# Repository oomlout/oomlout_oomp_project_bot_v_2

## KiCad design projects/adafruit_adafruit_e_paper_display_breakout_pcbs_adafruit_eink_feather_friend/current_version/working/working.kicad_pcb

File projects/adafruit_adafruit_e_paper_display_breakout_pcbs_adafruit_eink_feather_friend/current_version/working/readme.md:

# adafruit_e_paper_display_breakout_pcbs
 
## summary 
* id: adafruit_adafruit_e_paper_display_breakout_pcbs_adafruit_eink_feather_friend
* user: adafruit
* name: adafruit_e_paper_display_breakout_pcbs
* board: adafruit_eink_feather_friend
* repo: https://github.com/adafruit/Adafruit-E-Paper-Display-Breakout-PCBs

* src_file_repo_sch: 
* src_file_repo_sch_link: https://github.com/adafruit/Adafruit-E-Paper-Display-Breakout-PCBs/tree/master/
* full details link: https://github.com/oomlout/oomlout_oomp_project_bot_v_2/tree/main/projects/adafruit_adafruit_e_paper_display_breakout_pcbs_adafruit_eink_feather_friend/current_version/working  

## schematic  
  
[schematic (pdf)](working_schematic.pdf) 

## pcb  

[board (pdf)](working.pdf)  

## working_bom
| Id | Designator | Footprint | Quantity | Designation | Supplier and ref |  | None | 
| --- | --- | --- | --- | --- | --- | --- | --- | 
| 1 | U$5,U$3,U$4,U$6 | MOUNTINGHOLE_2.5_PLATED | 4 | MOUNTINGHOLE2.5 |  |  | [''] | 
| 2 | EINK1 | EINK_154IN | 1 | EINK_EPD0231EINK_154IN_200X200 |  |  | [''] | 
| 3 | X1 | MICROSD | 1 | MICROSD |  |  | [''] | 
| 4 | IC1 | TSSOP20 | 1 | 74LVC245PW |  |  | [''] | 
| 5 | R6,R1,R5,R2,R3 | 0805-NO | 5 | 100K |  |  | [''] | 
| 6 | C3,C4,C16,C22,C23 | 0805-NO | 5 | 1uF/25V |  |  | [''] | 
| 7 | FID3,FID2,FID1 | FIDUCIAL_1MM | 3 | FIDUCIAL_1MM |  |  | [''] | 
| 8 | C21,C20 | 0805-NO | 2 | 10ÂµF |  |  | [''] | 
| 9 | D3,D1,D2 | SOD-123 | 3 | MBR0530 |  |  | [''] | 
| 10 | U$28 | ADAFRUIT_TEXT_20MM | 1 |  |  |  | [''] | 
| 11 | L1 | INDUCTOR_4X4MM_NR401 | 1 | 10uH |  |  | [''] | 
| 12 | C6,C2 | 0805-NO | 2 | 1uF/10V |  |  | [''] | 
| 13 | R4 | 0805_10MGAP | 1 | 0.47ohm |  |  | [''] | 
| 14 | C24 | 0805-NO | 1 | 1uF/6V |  |  | [''] | 
| 15 | Q5 | SOT23-3 | 1 | IRLML0100 |  |  | [''] | 
| 16 | U2 | SOT23-5 | 1 | MIC5225-3.3 |  |  | [''] | 
| 17 | U$9 | PCBFEAT-REV-040 | 1 |  |  |  | [''] | 
| 18 | C15 | 0805-NO | 1 | 10uF/10V+ |  |  | [''] | 
| 19 | C1 | 0805_10MGAP | 1 | 1uF |  |  | [''] | 
| 20 | C5 | 0805-NO | 1 | 4.7uF/25V |  |  | [''] | 
| 21 | C8,C7 | 0805-NO | 2 | 1uF |  |  | [''] | 
| 22 | U4 | SOIC8_150MIL | 1 | 23K640-I/SN |  |  | [''] | 
| 23 | JP2 | 1X13_ROUND_70 | 1 |  |  |  | [''] | 

## bom_schematic
| Ref | Qnty | Value | Cmp name | Footprint | Description | Vendor | DNP | 
| --- | --- | --- | --- | --- | --- | --- | --- | 
| C1 | 1 | 1uF | CAP_CERAMIC0805_10MGAP | working:0805_10MGAP |  |  |  | 
| C2, C6 | 2 | 1uF/10V | CAP_CERAMIC0805-NOOUTLINE | working:0805-NO |  |  |  | 
| C3, C4, C16, C22, C23 | 5 | 1uF/25V | CAP_CERAMIC0805-NOOUTLINE | working:0805-NO |  |  |  | 
| C5 | 1 | 4.7uF/25V | CAP_CERAMIC0805-NOOUTLINE | working:0805-NO |  |  |  | 
| C7, C8 | 2 | 1uF | CAP_CERAMIC0805-NOOUTLINE | working:0805-NO |  |  |  | 
| C15 | 1 | 10uF/10V+ | CAP_CERAMIC0805-NOOUTLINE | working:0805-NO |  |  |  | 
| C20, C21 | 2 | 10ÂµF | CAP_CERAMIC0805-NOOUTLINE | working:0805-NO |  |  |  | 
| C24 | 1 | 1uF/6V | CAP_CERAMIC0805-NOOUTLINE | working:0805-NO |  |  |  | 
| D1, D2, D3 | 3 | MBR0530 | DIODE-SCHOTTKYSOD-123 | working:SOD-123 |  |  |  | 
| EINK1 | 1 | EINK_EPD0231EINK_154IN_200X200 | EINK_EPD0231EINK_154IN_200X200 | working:EINK_154IN |  |  |  | 
| FID1, FID2, FID3 | 3 | FIDUCIAL_1MM | FIDUCIAL_1MM | working:FIDUCIAL_1MM |  |  |  | 
| IC1 | 1 | 74245TSSOP20 | 74245TSSOP20 | working:TSSOP20 |  |  |  | 
| JP2 | 1 | HEADER-1X13 | HEADER-1X13 | working:1X13_ROUND_70 |  |  |  | 
| L1 | 1 | 10uH | INDUCTORNR401 | working:INDUCTOR_4X4MM_NR401 |  |  |  | 
| Q5 | 1 | IRLML2060TRPBF | IRLML2060TRPBF | working:SOT23-3 |  |  |  | 
| R1, R2, R3, R5, R6 | 5 | 100K | RESISTOR0805_NOOUTLINE | working:0805-NO |  |  |  | 
| R4 | 1 | 0.47ohm | RESISTOR0805_10MGAP | working:0805_10MGAP |  |  |  | 
| U2 | 1 | MIC5225-3.3 | VREG_SOT23-5 | working:SOT23-5 |  |  |  | 
| U4 | 1 | 23K640-I/SN | SRAM_SPI_SOIC8 | working:SOIC8_150MIL |  |  |  | 
| U$3, U$4, U$5, U$6 | 4 | MOUNTINGHOLE2.5 | MOUNTINGHOLE2.5 | working:MOUNTINGHOLE_2.5_PLATED |  |  |  | 
| X1 | 1 | MICROSD | MICROSD | working:MICROSD |  |  |  | 

## mounting_holes
| x | y | package | value | ref | size | 
| --- | --- | --- | --- | --- | --- | 
| 0.0 | 0.0 | MOUNTINGHOLE_2.5_PLATED | MOUNTINGHOLE2.5 | U$3 | m3 | 
| 38.1 | 0.0 | MOUNTINGHOLE_2.5_PLATED | MOUNTINGHOLE2.5 | U$4 | m3 | 
| 0.0 | 38.1 | MOUNTINGHOLE_2.5_PLATED | MOUNTINGHOLE2.5 | U$5 | m3 | 
| 38.1 | 38.1 | MOUNTINGHOLE_2.5_PLATED | MOUNTINGHOLE2.5 | U$6 | m3 |

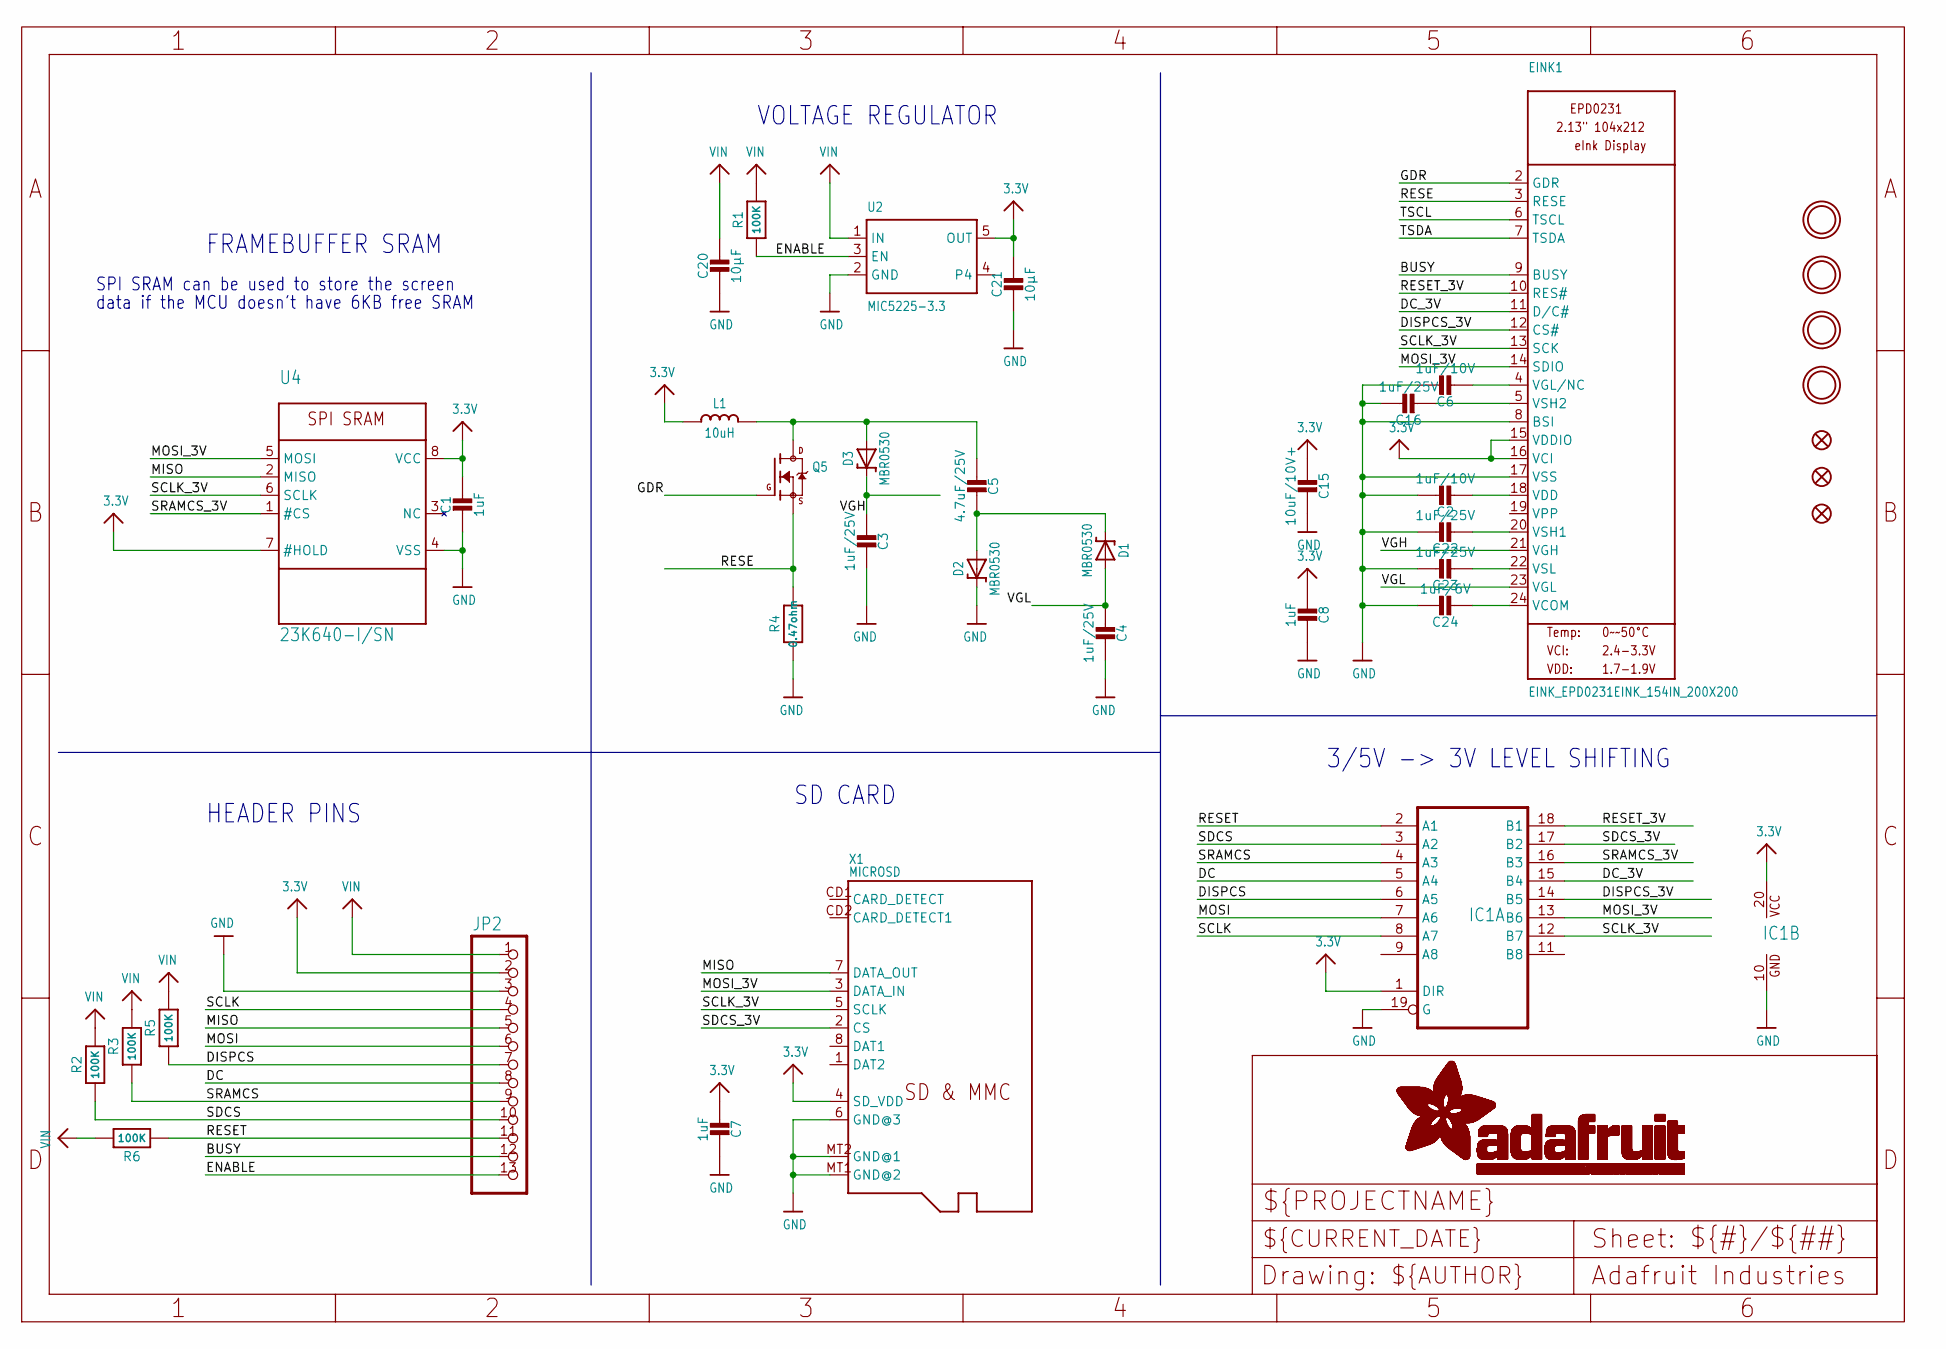
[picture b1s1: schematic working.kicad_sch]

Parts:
C1: 1uF; 0805_10MGAP
C2, C6: 1uF/10V; 0805-NO
C3, C4, C16, C22, C23: 1uF/25V; 0805-NO
C5: 4.7uF/25V; 0805-NO
C7, C8: 1uF; 0805-NO
C15: 10uF/10V+; 0805-NO
C20, C21: 10µF; 0805-NO
C24: 1uF/6V; 0805-NO
D1, D2, D3: MBR0530; SOD-123
EINK1: EINK_EPD0231EINK_154IN_200X200; EINK_154IN
FID1, FID2, FID3: FIDUCIAL_1MM
IC1: 74245TSSOP20; TSSOP20
JP2: HEADER-1X13; 1X13_ROUND_70
L1: 10uH; INDUCTOR_4X4MM_NR401
Q5: IRLML2060TRPBF; SOT23-3
R1, R2, R3, R5, R6: 100K; 0805-NO
R4: 0.47ohm; 0805_10MGAP
U2: MIC5225-3.3; SOT23-5
U4: 23K640-I/SN; SOIC8_150MIL
U$3, U$4, U$5, U$6: MOUNTINGHOLE2.5; MOUNTINGHOLE_2.5_PLATED
X1: MICROSD

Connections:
3.3V: C1.1, C7.1, C8.1, C15.2, C21.1, EINK1.15 (VDDIO), EINK1.16 (VCI), IC1.1 (DIR), IC1.20 (VCC), JP2.2, L1.P$2 (2), U2.5 (OUT), U4.7 (#HOLD), U4.8 (VCC), X1.4 (SD_VDD)
BUSY: EINK1.9 (BUSY), JP2.12
DC: IC1.5 (A4), JP2.8
DC_3V: EINK1.11 (D/C#), IC1.15 (B4)
DISPCS: IC1.6 (A5), JP2.7, R5.1
DISPCS_3V: EINK1.12 (CS#), IC1.14 (B5)
ENABLE: JP2.13, R1.1, U2.3 (EN)
GDR: EINK1.2 (GDR), Q5.1 (G)
GND: C1.2, C2.1, C3.2, C4.2, C6.1, C7.2, C8.2, C15.1, C16.1, C20.2, C21.2, C22.1, C23.1, C24.1, D2.C, EINK1.8 (BSI), EINK1.17 (VSS), IC1.10 (GND), IC1.19 (G), JP2.3, R4.2, U2.2 (GND), U4.4 (VSS), X1.6 (GND@3), X1.MT1 (GND@2), X1.MT2 (GND@1)
MISO: JP2.5, U4.2 (MISO), X1.7 (DATA_OUT)
MOSI: IC1.7 (A6), JP2.6
MOSI_3V: EINK1.14 (SDIO), IC1.13 (B6), U4.5 (MOSI), X1.3 (DATA_IN)
unnamed: C5.2, D1.C, D2.A
unnamed: C5.1, D3.A, L1.P$1 (1), Q5.3 (D)
unnamed: C16.2, EINK1.5 (VSH2)
unnamed: C2.2, EINK1.18 (VDD)
unnamed: C22.2, EINK1.20 (VSH1)
unnamed: C6.2, EINK1.4 (VGL/NC)
unnamed: C23.2, EINK1.22 (VSL)
unnamed: C24.2, EINK1.24 (VCOM)
RESE: EINK1.3 (RESE), Q5.2 (S), R4.1
RESET: IC1.2 (A1), JP2.11, R6.1
RESET_3V: EINK1.10 (RES#), IC1.18 (B1)
SCLK: IC1.8 (A7), JP2.4
SCLK_3V: EINK1.13 (SCK), IC1.12 (B7), U4.6 (SCLK), X1.5 (SCLK)
SDCS: IC1.3 (A2), JP2.10, R2.1
SDCS_3V: IC1.17 (B2), X1.2 (CS)
SRAMCS: IC1.4 (A3), JP2.9, R3.1
SRAMCS_3V: IC1.16 (B3), U4.1 (#CS)
TSCL: EINK1.6 (TSCL)
TSDA: EINK1.7 (TSDA)
VGH: C3.1, D3.C, EINK1.21 (VGH)
VGL: C4.1, D1.A, EINK1.23 (VGL)
VIN: C20.1, JP2.1, R1.2, R2.2, R3.2, R5.2, R6.2, U2.1 (IN)

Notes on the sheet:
HEADER PINS
VOLTAGE REGULATOR
SPI SRAM can be used to store the screen
FRAMEBUFFER SRAM
3/5V -> 3V LEVEL SHIFTING
SD CARD
data if the MCU doesn't have 6KB free SRAM

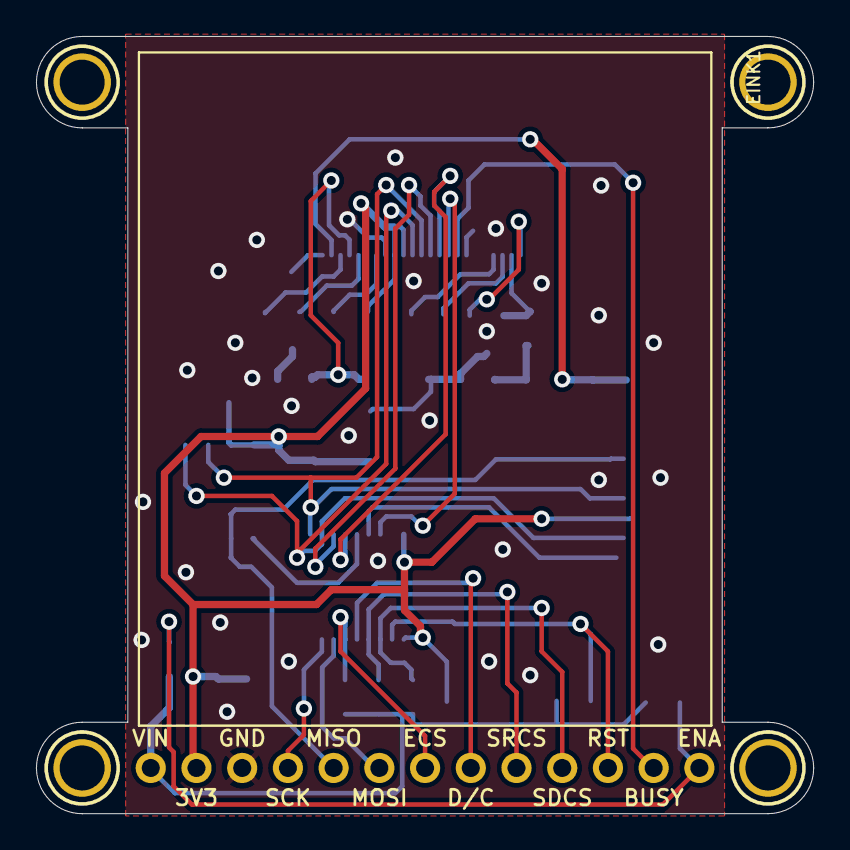
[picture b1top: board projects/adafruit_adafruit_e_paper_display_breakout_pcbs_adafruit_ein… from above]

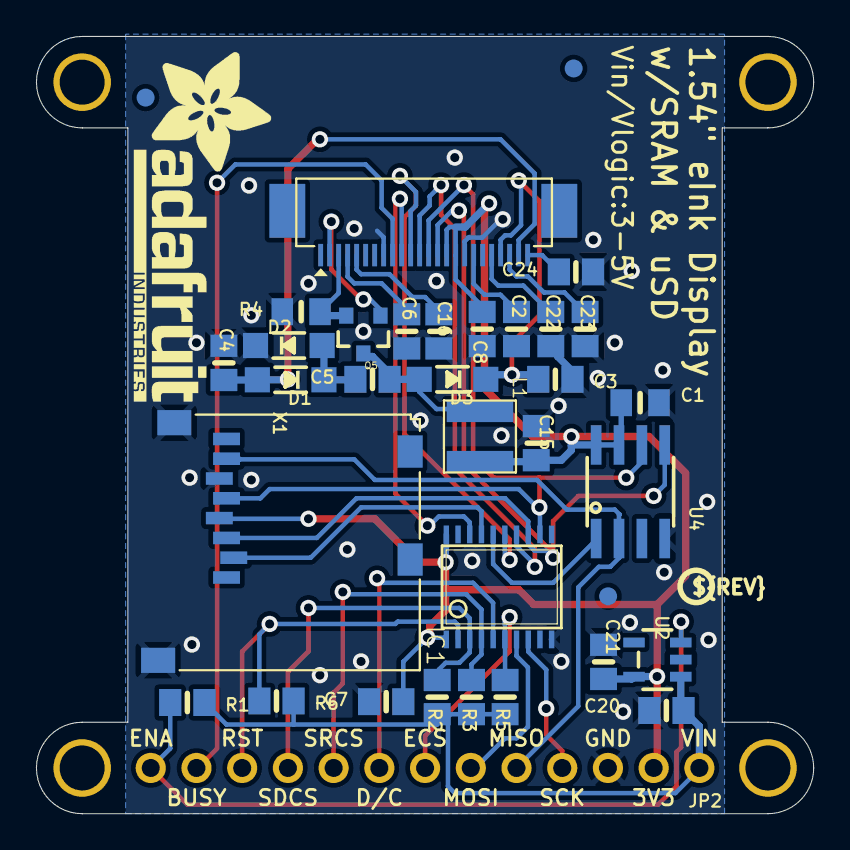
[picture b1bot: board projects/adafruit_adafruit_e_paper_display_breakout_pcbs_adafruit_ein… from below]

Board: 2 copper layers, 43.2 x 43.2 mm, 41 parts (36 on the bottom side), 32 nets.

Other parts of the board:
U$9: PCBFEAT-REV-040
U$28: ADAFRUIT_TEXT_20MM

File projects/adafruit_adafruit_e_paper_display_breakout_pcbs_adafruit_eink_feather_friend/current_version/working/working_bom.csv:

"Id";"Designator";"Footprint";"Quantity";"Designation";"Supplier and ref";
1;"U$5,U$3,U$4,U$6";"MOUNTINGHOLE_2.5_PLATED";4;"MOUNTINGHOLE2.5";;;
2;"EINK1";"EINK_154IN";1;"EINK_EPD0231EINK_154IN_200X200";;;
3;"X1";"MICROSD";1;"MICROSD";;;
4;"IC1";"TSSOP20";1;"74LVC245PW";;;
5;"R6,R1,R5,R2,R3";"0805-NO";5;"100K";;;
6;"C3,C4,C16,C22,C23";"0805-NO";5;"1uF/25V";;;
7;"FID3,FID2,FID1";"FIDUCIAL_1MM";3;"FIDUCIAL_1MM";;;
8;"C21,C20";"0805-NO";2;"10µF";;;
9;"D3,D1,D2";"SOD-123";3;"MBR0530";;;
10;"U$28";"ADAFRUIT_TEXT_20MM";1;"";;;
11;"L1";"INDUCTOR_4X4MM_NR401";1;"10uH";;;
12;"C6,C2";"0805-NO";2;"1uF/10V";;;
13;"R4";"0805_10MGAP";1;"0.47ohm";;;
14;"C24";"0805-NO";1;"1uF/6V";;;
15;"Q5";"SOT23-3";1;"IRLML0100";;;
16;"U2";"SOT23-5";1;"MIC5225-3.3";;;
17;"U$9";"PCBFEAT-REV-040";1;"";;;
18;"C15";"0805-NO";1;"10uF/10V+";;;
19;"C1";"0805_10MGAP";1;"1uF";;;
20;"C5";"0805-NO";1;"4.7uF/25V";;;
21;"C8,C7";"0805-NO";2;"1uF";;;
22;"U4";"SOIC8_150MIL";1;"23K640-I/SN";;;
23;"JP2";"1X13_ROUND_70";1;"";;;

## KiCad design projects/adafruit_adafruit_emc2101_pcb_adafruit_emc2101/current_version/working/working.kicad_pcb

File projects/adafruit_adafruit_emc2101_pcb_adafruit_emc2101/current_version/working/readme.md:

# adafruit_emc2101_pcb
 
## summary 
* id: adafruit_adafruit_emc2101_pcb_adafruit_emc2101
* user: adafruit
* name: adafruit_emc2101_pcb
* board: adafruit_emc2101
* repo: https://github.com/adafruit/Adafruit-EMC2101-PCB

* src_file_repo_sch: 
* src_file_repo_sch_link: https://github.com/adafruit/Adafruit-EMC2101-PCB/tree/main/
* full details link: https://github.com/oomlout/oomlout_oomp_project_bot_v_2/tree/main/projects/adafruit_adafruit_emc2101_pcb_adafruit_emc2101/current_version/working  

## schematic  
  
[schematic (pdf)](working_schematic.pdf) 

## pcb  

[board (pdf)](working.pdf)  

## working_bom
| Id | Designator | Footprint | Quantity | Designation | Supplier and ref |  | None | 
| --- | --- | --- | --- | --- | --- | --- | --- | 
| 1 | JP1 | 1X06_ROUND_70 | 1 |  |  |  | [''] | 
| 2 | JP2 | 1X04_ROUND | 1 |  |  |  | [''] | 
| 3 | CONN3,CONN4 | JST_SH4 | 2 | STEMMA_I2C_QT |  |  | [''] | 
| 4 | R1 | _0603MP | 1 | 10K |  |  | [''] | 
| 5 | FID4,FID3 | FIDUCIAL_1MM | 2 | FIDUCIAL_1MM |  |  | [''] | 
| 6 | C3,C2 | 0805-NO | 2 | 10uF |  |  | [''] | 
| 7 | U$1,U$21,U$19,U$17 | MOUNTINGHOLE_2.5_PLATED | 4 | MOUNTINGHOLE2.5 |  |  | [''] | 
| 8 | C1 | 0603-NO | 1 | 0.1uF |  |  | [''] | 
| 9 | D1 | CHIPLED_0603_NOOUTLINE | 1 | GREEN |  |  | [''] | 
| 10 | U2 | SOT23-5 | 1 | AP2112K-3.3 |  |  | [''] | 
| 11 | R3 | RESPACK_4X0603 | 1 | 10K |  |  | [''] | 
| 12 | X1 | MSOP8_0.65MM | 1 | EMC2101-AZCL |  |  | [''] | 
| 13 | U$22 | ADAFRUIT_3.5MM | 1 |  |  |  | [''] | 
| 14 | SJ1 | SOLDERJUMPER_CLOSEDWIRE | 1 | FAN |  |  | [''] | 
| 15 | U$31,U$30 | STEMMAQT | 2 |  |  |  | [''] | 
| 16 | U$25 | PCBFEAT-REV-040 | 1 |  |  |  | [''] | 
| 17 | SJ2 | SOLDERJUMPER_ARROW_NOPASTE | 1 | TACH |  |  | [''] | 

## bom_schematic
| Ref | Qnty | Value | Cmp name | Footprint | Description | Vendor | DNP | 
| --- | --- | --- | --- | --- | --- | --- | --- | 
| C1 | 1 | 0.1uF | CAP_CERAMIC0603_NO | working:0603-NO |  |  |  | 
| C2, C3 | 2 | 10uF | CAP_CERAMIC0805-NOOUTLINE | working:0805-NO |  |  |  | 
| CONN3, CONN4 | 2 | STEMMA_I2C_QT | STEMMA_I2C_QT | working:JST_SH4 |  |  |  | 
| D1 | 1 | GREEN | LED0603_NOOUTLINE | working:CHIPLED_0603_NOOUTLINE |  |  |  | 
| FID3, FID4 | 2 | FIDUCIAL_1MM | FIDUCIAL_1MM | working:FIDUCIAL_1MM |  |  |  | 
| JP1 | 1 | HEADER-1X670MIL | HEADER-1X670MIL | working:1X06_ROUND_70 |  |  |  | 
| JP2 | 1 | HEADER-1X4ROUND | HEADER-1X4ROUND | working:1X04_ROUND |  |  |  | 
| R1 | 1 | 10K | RESISTOR_0603MP | working:_0603MP |  |  |  | 
| R3 | 1 | 10K | RESISTOR_4PACK | working:RESPACK_4X0603 |  |  |  | 
| SJ1 | 1 | FAN | SOLDERJUMPERCLOSED | working:SOLDERJUMPER_CLOSEDWIRE |  |  |  | 
| SJ2 | 1 | TACH | SOLDERJUMPER | working:SOLDERJUMPER_ARROW_NOPASTE |  |  |  | 
| U2 | 1 | AP2112K-3.3 | VREG_SOT23-5 | working:SOT23-5 |  |  |  | 
| U$1, U$17, U$19, U$21 | 4 | MOUNTINGHOLE2.5 | MOUNTINGHOLE2.5 | working:MOUNTINGHOLE_2.5_PLATED |  |  |  | 
| X1 | 1 | EMC2101-AZCL | EMC2101-AZCL | working:MSOP8_0.65MM |  |  |  | 

## mounting_holes
| x | y | package | value | ref | size | 
| --- | --- | --- | --- | --- | --- | 
| 0.0 | 12.7 | MOUNTINGHOLE_2.5_PLATED | MOUNTINGHOLE2.5 | U$1 | m3 | 
| 20.32 | 12.7 | MOUNTINGHOLE_2.5_PLATED | MOUNTINGHOLE2.5 | U$17 | m3 | 
| 0.0 | 0.0 | MOUNTINGHOLE_2.5_PLATED | MOUNTINGHOLE2.5 | U$19 | m3 | 
| 20.32 | 0.0 | MOUNTINGHOLE_2.5_PLATED | MOUNTINGHOLE2.5 | U$21 | m3 |

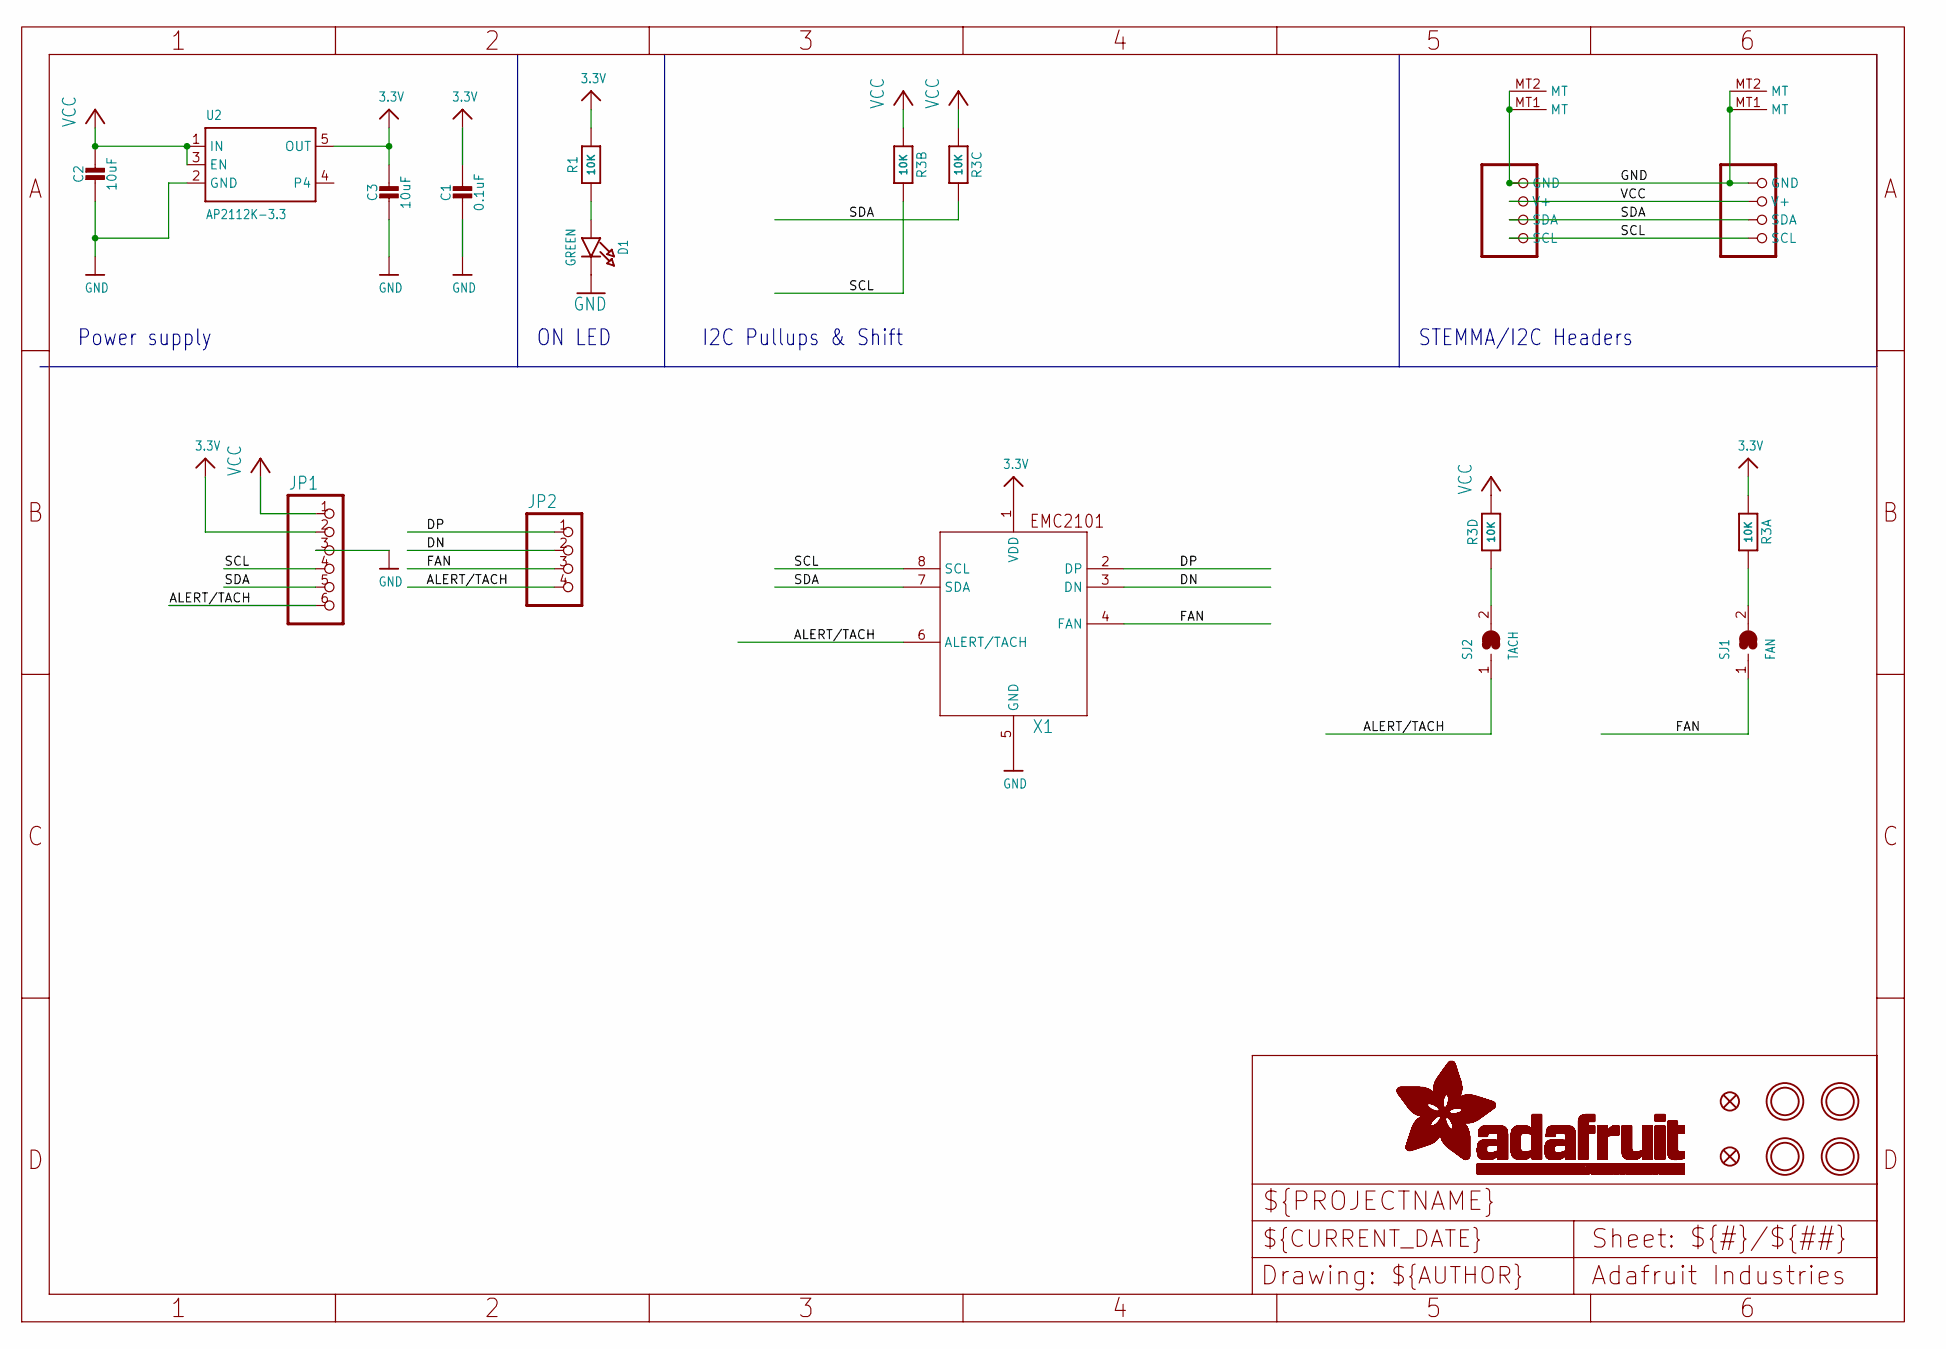
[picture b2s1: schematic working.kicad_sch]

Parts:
C1: 0.1uF; 0603-NO
C2, C3: 10uF; 0805-NO
CONN3, CONN4: STEMMA_I2C_QT; JST_SH4
D1: GREEN; CHIPLED_0603_NOOUTLINE
FID3, FID4: FIDUCIAL_1MM
JP1: HEADER-1X670MIL; 1X06_ROUND_70
JP2: HEADER-1X4ROUND; 1X04_ROUND
R1: 10K; _0603MP
R3: 10K; RESPACK_4X0603
SJ1: FAN; SOLDERJUMPER_CLOSEDWIRE
SJ2: TACH; SOLDERJUMPER_ARROW_NOPASTE
U2: AP2112K-3.3; SOT23-5
U$1, U$17, U$19, U$21: MOUNTINGHOLE2.5; MOUNTINGHOLE_2.5_PLATED
X1: EMC2101-AZCL; MSOP8_0.65MM

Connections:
3.3V: C1.1, C3.1, JP1.2, R1.2, R3.1, U2.5 (OUT), X1.1 (VDD)
ALERT/TACH: JP1.6, JP2.4, SJ2.1, X1.6 (ALERT/TACH)
DN: JP2.2, X1.3 (DN)
DP: JP2.1, X1.2 (DP)
FAN: JP2.3, SJ1.1, X1.4 (FAN)
GND: C1.2, C2.2, C3.2, CONN3.1 (GND), CONN3.MT1 (MT), CONN3.MT2 (MT), CONN4.1 (GND), CONN4.MT1 (MT), CONN4.MT2 (MT), D1.C, JP1.3, U2.2 (GND), X1.5 (GND)
unnamed: R3.4 (1), SJ2.2
unnamed: R3.8 (2), SJ1.2
unnamed: D1.A, R1.1
SCL: CONN3.4 (SCL), CONN4.4 (SCL), JP1.4, R3.7 (2), X1.8 (SCL)
SDA: CONN3.3 (SDA), CONN4.3 (SDA), JP1.5, R3.6 (2), X1.7 (SDA)
VCC: C2.1, CONN3.2 (V+), CONN4.2 (V+), JP1.1, R3.2 (1), R3.3 (1), R3.5 (2), U2.1 (IN), U2.3 (EN)

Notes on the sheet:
ON LED
Power supply
I2C Pullups & Shift
STEMMA/I2C Headers

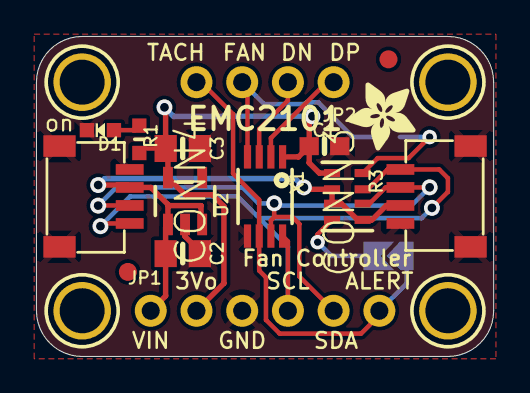
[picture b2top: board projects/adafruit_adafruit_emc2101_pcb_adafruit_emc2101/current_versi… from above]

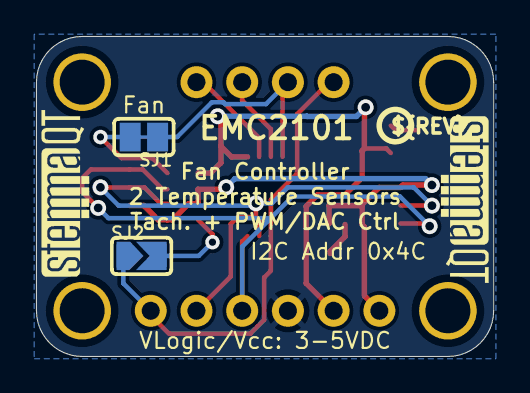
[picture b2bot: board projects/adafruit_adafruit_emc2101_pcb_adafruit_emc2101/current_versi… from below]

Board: 2 copper layers, 25.4 x 17.8 mm, 24 parts (5 on the bottom side), 12 nets.

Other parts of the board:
U$22: ADAFRUIT_3.5MM
U$25: PCBFEAT-REV-040
U$30, U$31: STEMMAQT

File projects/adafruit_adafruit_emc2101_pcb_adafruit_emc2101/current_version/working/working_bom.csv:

"Id";"Designator";"Footprint";"Quantity";"Designation";"Supplier and ref";
1;"JP1";"1X06_ROUND_70";1;"";;;
2;"JP2";"1X04_ROUND";1;"";;;
3;"CONN3,CONN4";"JST_SH4";2;"STEMMA_I2C_QT";;;
4;"R1";"_0603MP";1;"10K";;;
5;"FID4,FID3";"FIDUCIAL_1MM";2;"FIDUCIAL_1MM";;;
6;"C3,C2";"0805-NO";2;"10uF";;;
7;"U$1,U$21,U$19,U$17";"MOUNTINGHOLE_2.5_PLATED";4;"MOUNTINGHOLE2.5";;;
8;"C1";"0603-NO";1;"0.1uF";;;
9;"D1";"CHIPLED_0603_NOOUTLINE";1;"GREEN";;;
10;"U2";"SOT23-5";1;"AP2112K-3.3";;;
11;"R3";"RESPACK_4X0603";1;"10K";;;
12;"X1";"MSOP8_0.65MM";1;"EMC2101-AZCL";;;
13;"U$22";"ADAFRUIT_3.5MM";1;"";;;
14;"SJ1";"SOLDERJUMPER_CLOSEDWIRE";1;"FAN";;;
15;"U$31,U$30";"STEMMAQT";2;"";;;
16;"U$25";"PCBFEAT-REV-040";1;"";;;
17;"SJ2";"SOLDERJUMPER_ARROW_NOPASTE";1;"TACH";;;

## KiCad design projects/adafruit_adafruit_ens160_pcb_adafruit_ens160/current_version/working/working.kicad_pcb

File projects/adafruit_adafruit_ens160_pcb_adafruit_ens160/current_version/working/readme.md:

# adafruit_ens160_pcb
 
## summary 
* id: adafruit_adafruit_ens160_pcb_adafruit_ens160
* user: adafruit
* name: adafruit_ens160_pcb
* board: adafruit_ens160
* repo: https://github.com/adafruit/Adafruit-ENS160-PCB

* src_file_repo_sch: 
* src_file_repo_sch_link: https://github.com/adafruit/Adafruit-ENS160-PCB/tree/main/
* full details link: https://github.com/oomlout/oomlout_oomp_project_bot_v_2/tree/main/projects/adafruit_adafruit_ens160_pcb_adafruit_ens160/current_version/working  

## schematic  
  
[schematic (pdf)](working_schematic.pdf) 

## pcb  

[board (pdf)](working.pdf)  

## working_bom
| Id | Designator | Footprint | Quantity | Designation | Supplier and ref |  | None | 
| --- | --- | --- | --- | --- | --- | --- | --- | 
| 1 | FID4,FID3 | FIDUCIAL_1MM | 2 | FIDUCIAL_1MM |  |  | [''] | 
| 2 | X1 | ENS160 | 1 | ENS160 |  |  | [''] | 
| 3 | JP2 | 1X08_ROUND_70 | 1 |  |  |  | [''] | 
| 4 | U$1,U$17 | MOUNTINGHOLE_2.5_PLATED | 2 | MOUNTINGHOLE2.5 |  |  | [''] | 
| 5 | D2 | SOD-323 | 1 | 1N4148 |  |  | [''] | 
| 6 | R3 | RESPACK_4X0603 | 1 | 10K pack |  |  | [''] | 
| 7 | C3,C4,C2 | 0805-NO | 3 | 10uF |  |  | [''] | 
| 8 | U$20 | ADAFRUIT_3.5MM | 1 |  |  |  | [''] | 
| 9 | R5,R4,R1 | 0603-NO | 3 | 10K |  |  | [''] | 
| 10 | CONN4,CONN3 | JST_SH4 | 2 | STEMMA_I2C_QT |  |  | [''] | 
| 11 | U1 | SOT23-6 | 1 | AP7312-1833 |  |  | [''] | 
| 12 | D1 | CHIPLED_0603_NOOUTLINE | 1 | GREEN |  |  | [''] | 
| 13 | Q2 | SOT363 | 1 | BSS138 |  |  | [''] | 
| 14 | C1 | 0603-NO | 1 | 0.1uF |  |  | [''] | 
| 15 | U$25 | PCBFEAT-REV-040 | 1 |  |  |  | [''] | 
| 16 | U$30,U$31 | STEMMAQT | 2 |  |  |  | [''] | 
| 17 | SJ1 | SOLDERJUMPER_ARROW_NOPASTE | 1 |  |  |  | [''] | 

## bom_schematic
| Ref | Qnty | Value | Cmp name | Footprint | Description | Vendor | DNP | 
| --- | --- | --- | --- | --- | --- | --- | --- | 
| C1 | 1 | 0.1uF | CAP_CERAMIC0603_NO | working:0603-NO |  |  |  | 
| C2, C3, C4 | 3 | 10uF | CAP_CERAMIC0805-NOOUTLINE | working:0805-NO |  |  |  | 
| CONN3, CONN4 | 2 | STEMMA_I2C_QT | STEMMA_I2C_QT | working:JST_SH4 |  |  |  | 
| D1 | 1 | GREEN | LED0603_NOOUTLINE | working:CHIPLED_0603_NOOUTLINE |  |  |  | 
| D2 | 1 | 1N4148 | DIODESOD-323 | working:SOD-323 |  |  |  | 
| FID3, FID4 | 2 | FIDUCIAL_1MM | FIDUCIAL_1MM | working:FIDUCIAL_1MM |  |  |  | 
| JP2 | 1 | HEADER-1X870MIL | HEADER-1X870MIL | working:1X08_ROUND_70 |  |  |  | 
| Q2 | 1 | BSS138 | MOSFET-N_DUAL | working:SOT363 |  |  |  | 
| R1, R4, R5 | 3 | 10K | RESISTOR_0603_NOOUT | working:0603-NO |  |  |  | 
| R3 | 1 | 10K pack | RESISTOR_4PACK | working:RESPACK_4X0603 |  |  |  | 
| SJ1 | 1 | SOLDERJUMPER | SOLDERJUMPER | working:SOLDERJUMPER_ARROW_NOPASTE |  |  |  | 
| U1 | 1 | AP7312-1833 | VREG_SOT23-6_DUALAP7312 | working:SOT23-6 |  |  |  | 
| U$1, U$17 | 2 | MOUNTINGHOLE2.5 | MOUNTINGHOLE2.5 | working:MOUNTINGHOLE_2.5_PLATED |  |  |  | 
| X1 | 1 | ENS160 | ENS160 | working:ENS160 |  |  |  | 

## mounting_holes
| x | y | package | value | ref | size | 
| --- | --- | --- | --- | --- | --- | 
| 0.0 | 0.0 | MOUNTINGHOLE_2.5_PLATED | MOUNTINGHOLE2.5 | U$1 | m3 | 
| 20.32 | 0.0 | MOUNTINGHOLE_2.5_PLATED | MOUNTINGHOLE2.5 | U$17 | m3 |

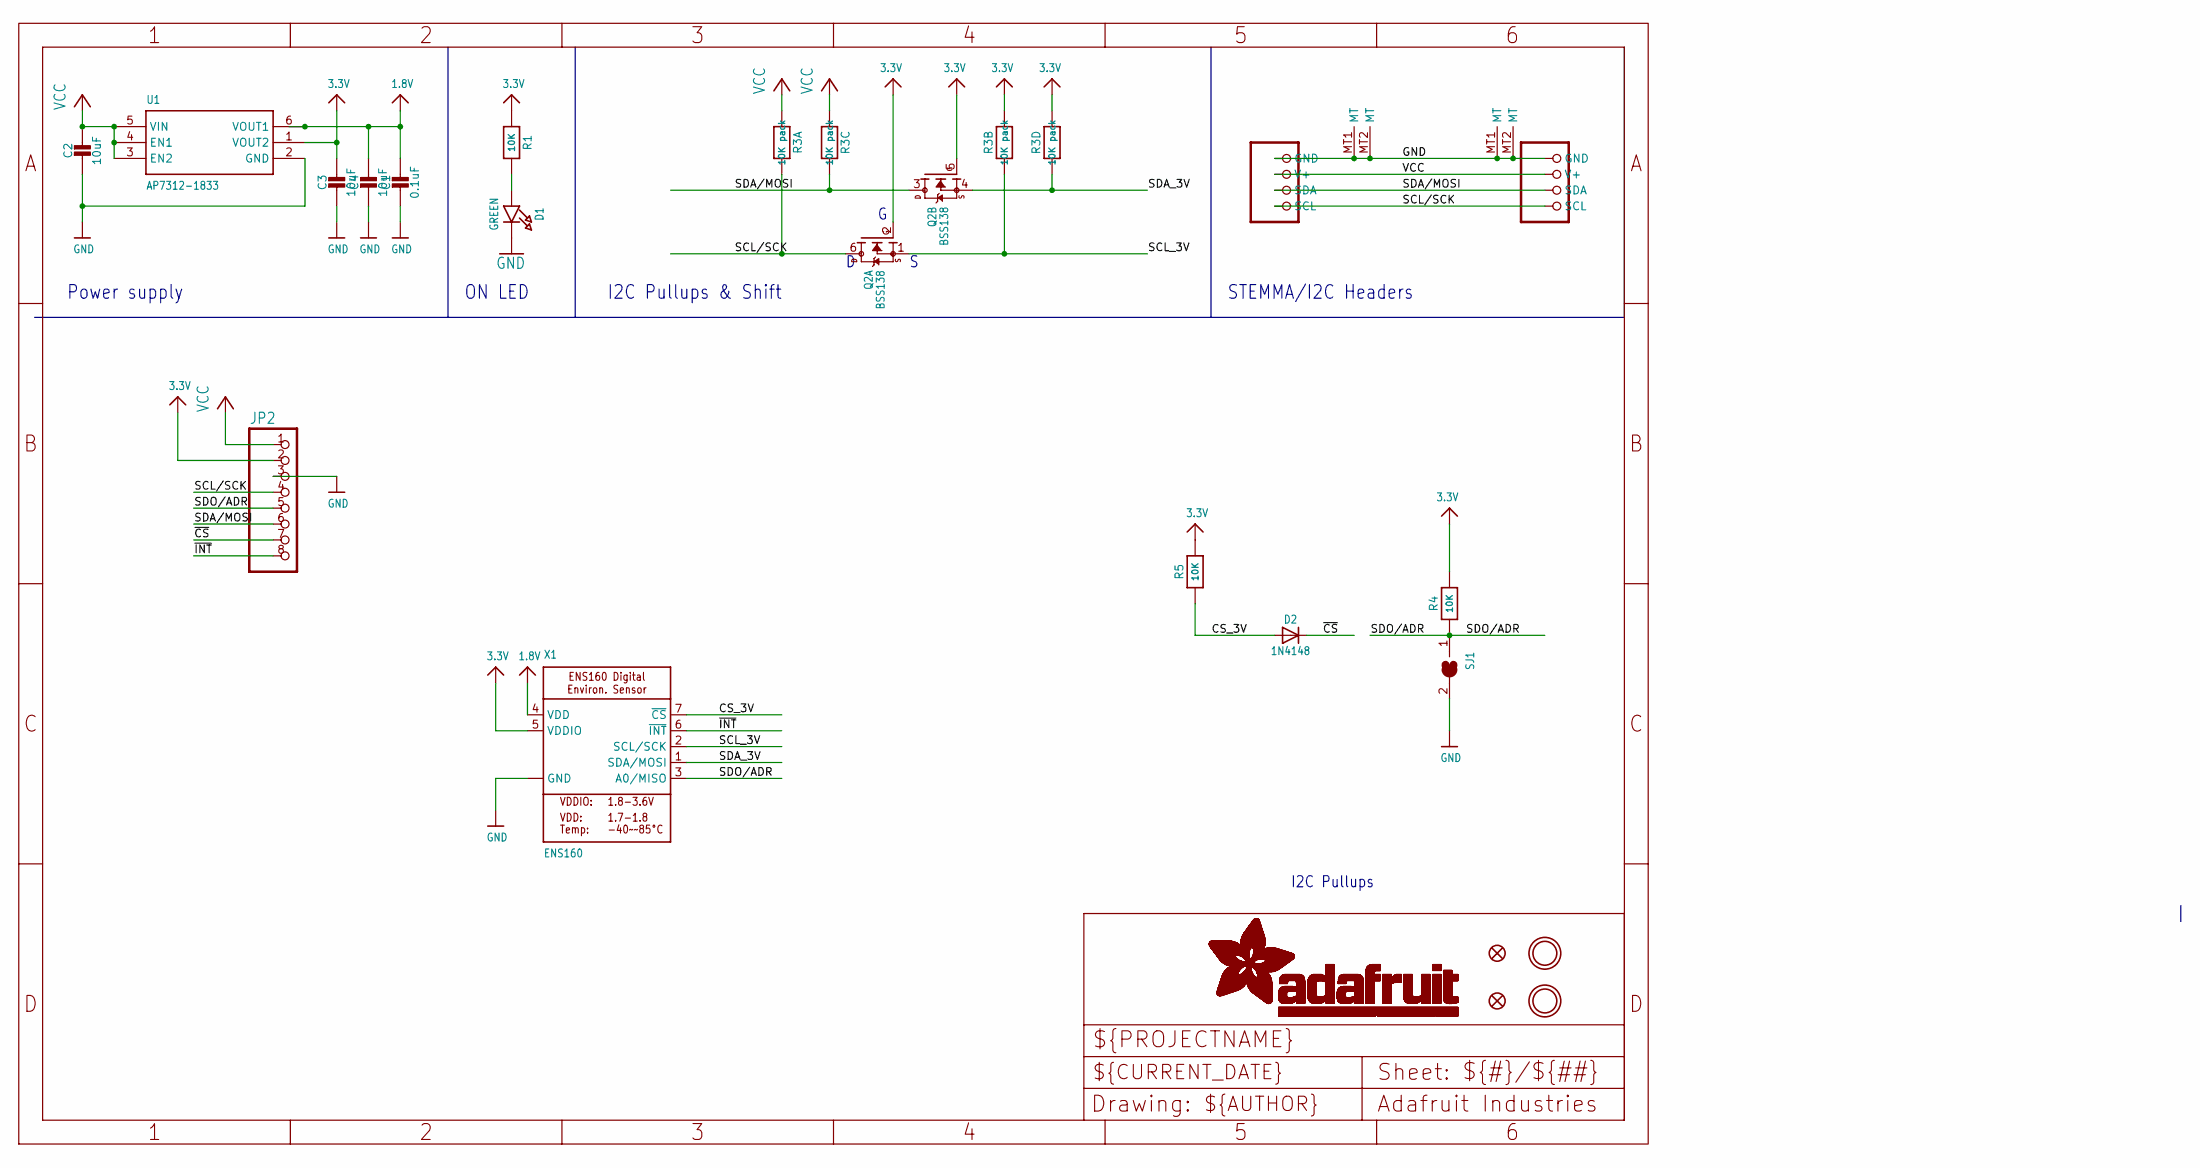
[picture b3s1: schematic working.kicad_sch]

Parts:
C1: 0.1uF; 0603-NO
C2, C3, C4: 10uF; 0805-NO
CONN3, CONN4: STEMMA_I2C_QT; JST_SH4
D1: GREEN; CHIPLED_0603_NOOUTLINE
D2: 1N4148; SOD-323
FID3, FID4: FIDUCIAL_1MM
JP2: HEADER-1X870MIL; 1X08_ROUND_70
Q2: BSS138; SOT363
R1, R4, R5: 10K; 0603-NO
R3: 10K pack; RESPACK_4X0603
SJ1: SOLDERJUMPER; SOLDERJUMPER_ARROW_NOPASTE
U1: AP7312-1833; SOT23-6
U$1, U$17: MOUNTINGHOLE2.5; MOUNTINGHOLE_2.5_PLATED
X1: ENS160

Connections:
1.8V: C1.1, C4.1, U1.6 (VOUT1), X1.4 (VDD)
3.3V: C3.1, JP2.2, Q2.2 (G), Q2.5 (G), R1.1, R3.2 (1), R3.4 (1), R4.2, R5.2, U1.1 (VOUT2), X1.5 (VDDIO)
CS_3V: D2.A, R5.1, X1.7 (~CS)
GND: C1.2, C2.2, C3.2, C4.2, CONN3.1 (GND), CONN3.MT1 (MT), CONN3.MT2 (MT), CONN4.1 (GND), CONN4.MT1 (MT), CONN4.MT2 (MT), D1.C, JP2.3, SJ1.2, U1.2 (GND), X1.8 (GND), X1.9 (GND)
unnamed: D1.A, R1.2
SCL/SCK: CONN3.4 (SCL), CONN4.4 (SCL), JP2.4, Q2.6 (D), R3.8 (2)
SCL_3V: Q2.1 (S), R3.7 (2), X1.2 (SCL/SCK)
SDA/MOSI: CONN3.3 (SDA), CONN4.3 (SDA), JP2.6, Q2.3 (D), R3.6 (2)
SDA_3V: Q2.4 (S), R3.5 (2), X1.1 (SDA/MOSI)
SDO/ADR: JP2.5, R4.1, SJ1.1, X1.3 (A0/MISO)
VCC: C2.1, CONN3.2 (V+), CONN4.2 (V+), JP2.1, R3.1, R3.3 (1), U1.3 (EN2), U1.4 (EN1), U1.5 (VIN)
~CS: D2.C, JP2.7
~INT: JP2.8, X1.6 (~INT)

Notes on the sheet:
I2C Pullups & Shift
I2C Pullups
Power supply
ON LED
STEMMA/I2C Headers

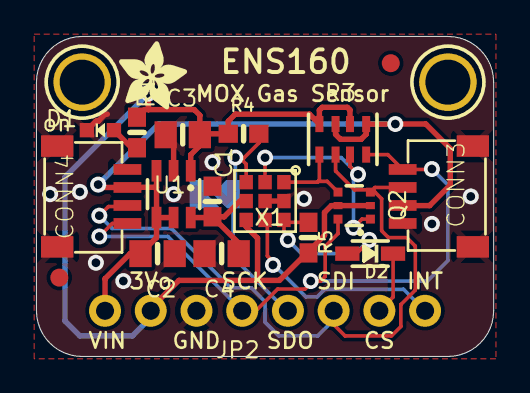
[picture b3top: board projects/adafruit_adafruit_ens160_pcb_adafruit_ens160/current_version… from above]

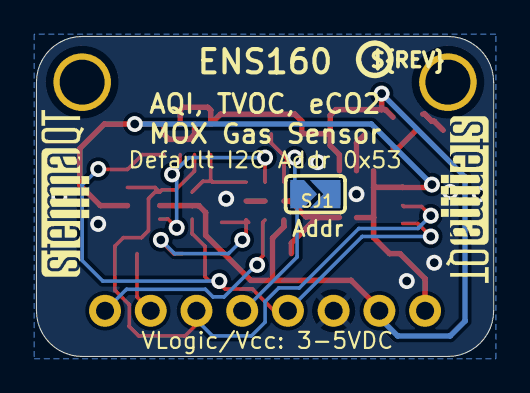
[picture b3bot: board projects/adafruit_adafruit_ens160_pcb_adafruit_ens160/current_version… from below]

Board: 2 copper layers, 25.4 x 17.8 mm, 25 parts (4 on the bottom side), 13 nets.

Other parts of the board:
U$20: ADAFRUIT_3.5MM
U$25: PCBFEAT-REV-040
U$30, U$31: STEMMAQT

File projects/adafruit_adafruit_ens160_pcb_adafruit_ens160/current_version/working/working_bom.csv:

"Id";"Designator";"Footprint";"Quantity";"Designation";"Supplier and ref";
1;"FID4,FID3";"FIDUCIAL_1MM";2;"FIDUCIAL_1MM";;;
2;"X1";"ENS160";1;"ENS160";;;
3;"JP2";"1X08_ROUND_70";1;"";;;
4;"U$1,U$17";"MOUNTINGHOLE_2.5_PLATED";2;"MOUNTINGHOLE2.5";;;
5;"D2";"SOD-323";1;"1N4148";;;
6;"R3";"RESPACK_4X0603";1;"10K pack";;;
7;"C3,C4,C2";"0805-NO";3;"10uF";;;
8;"U$20";"ADAFRUIT_3.5MM";1;"";;;
9;"R5,R4,R1";"0603-NO";3;"10K";;;
10;"CONN4,CONN3";"JST_SH4";2;"STEMMA_I2C_QT";;;
11;"U1";"SOT23-6";1;"AP7312-1833";;;
12;"D1";"CHIPLED_0603_NOOUTLINE";1;"GREEN";;;
13;"Q2";"SOT363";1;"BSS138";;;
14;"C1";"0603-NO";1;"0.1uF";;;
15;"U$25";"PCBFEAT-REV-040";1;"";;;
16;"U$30,U$31";"STEMMAQT";2;"";;;
17;"SJ1";"SOLDERJUMPER_ARROW_NOPASTE";1;"";;;
